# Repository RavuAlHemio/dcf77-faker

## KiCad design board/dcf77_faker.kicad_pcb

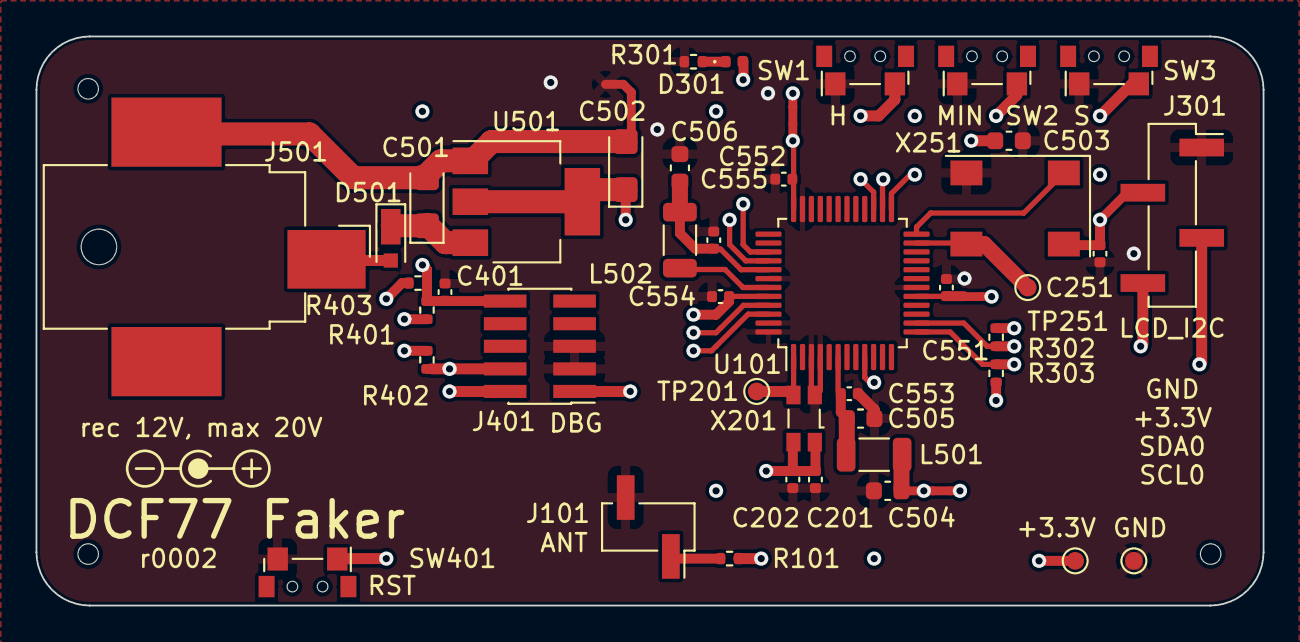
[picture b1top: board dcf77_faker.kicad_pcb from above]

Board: 4 copper layers, 69.0 x 32.0 mm, 46 parts (0 on the bottom side), 27 nets.

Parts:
C201, C202, C251, C401, C551, C552, C553, C554, C555: 100nF; C_0402_1005Metric
C501, C502: 10µF; CP_EIA-3216-18_Kemet-A
C503, C504, C505: 10µF; C_0603_1608Metric
C506: 1µF; C_0603_1608Metric
D301: LED; LED_0402_1005Metric
D501: MSS1P3L-M3/89A; D_MicroSMP_AK
J101: ANT; PinHeader_1x02_P2.54mm_Vertical_SMD_Pin1Right
J301: LCD_I2C; PinHeader_1x04_P2.54mm_Vertical_SMD_Pin1Right
J401: DBG; PinHeader_2x05_P1.27mm_Vertical_SMD
J501: Barrel_Jack; BarrelJack_CUI_PJ-036AH-SMT_Horizontal
L501, L502: 10µH; L_1206_3216Metric
NT501, NT502, NT503, NT504: NetTie_2; NetTie-2_SMD_Pad0.5mm
R101, R402: 1kΩ; R_0402_1005Metric
R301, R401: 330Ω; R_0402_1005Metric
R302, R303: 1.5kΩ; R_0402_1005Metric
R403: 2.2kΩ; R_0402_1005Metric
SW1: H; Shou_Han_TS24CA
SW2: MIN; Shou_Han_TS24CA
SW3: S; Shou_Han_TS24CA
SW401: RST; Shou_Han_TS24CA
TP201, TP251, TP501, TP502: TestPoint; TestPoint_Pad_D1.0mm
U101: ATSAML21G18B-AUT; TQFP-48_7x7mm_P0.5mm
U501: NCP1117ST33T3G; SOT-223-3_TabPin2
X201: 32.768kHz; Oscillator_SMD_SeikoEpson_SG3030CM
X251: 31MHz; Oscillator_SMD_Microchip_DSC8001A-6Pin_7.0x5.0mm_HandSolder

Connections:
/+3.3V: C201.2, C202.2, C251.2, C502.1, J301.2, J401.1, NT502.2, NT504.2, R302.1, R303.1, R402.2, R403.2, TP501.1, U501.2 (VO), X201.1 (VIO), X201.4 (Vcc), X251.4 (Vcc)
/GND: C201.1, C202.1, C251.1, C401.1, C503.2, C504.2, C505.2, C506.2, C551.2, C552.2, C553.2, C554.2, C555.2, J101.2, J301.1, J401.3, J401.5, NT501.2, R301.1, SW1.1, SW2.1, SW3.1, SW401.2, TP502.1, U101.3 (PA02), U101.4 (PA03), U101.18 (GND), U101.35 (GND), U101.42 (GND), U101.47 (PB02), U101.48 (PB03), X201.2 (GND), X251.2 (GND)
/H: SW1.2, U101.27 (PA18)
/LED: D301.2 (A), U101.39 (PA27)
/MIN: SW2.2, U101.26 (PA17)
/S: SW3.2, U101.25 (PA16)
/SCL0: J301.4, R302.2, U101.14 (PA09)
/SDA0: J301.3, R303.2, U101.13 (PA08)
/TCC0WO0: R101.2, U101.9 (PA04)
/VDDANA: C505.1, C553.1, L501.2, U101.6 (VDDANA)
/VDDCORE: C506.1, C555.1, L502.1, U101.41 (VDDCORE)
/VDDIN: C504.1, C554.1, L501.1, NT504.1, U101.44 (VDDIN)
/VDDIO1: C551.1, NT503.2, U101.17 (VDDIO1)
/VDDIO2: C503.1, C552.1, NT502.1, NT503.1, U101.36 (VDDIO2)
/VSW: L502.2, U101.43 (VSW)
/XIN: TP251.1, U101.23 (PA14), X251.3 (OUT)
/XIN32: TP201.1, U101.1 (PA00), X201.3 (OUT)
/X~ST: U101.24 (PA15), X251.1 (~ST)
/debug & reset/SWCLK: J401.4, R402.1, U101.45 (PA30)
/debug & reset/SWDIO: J401.2, U101.46 (PA31)
/debug & reset/~RST: C401.2, J401.10, R401.1, R403.1, U101.40 (~RESET)
/power supply/RAWGND: C501.2, C502.2, J501.2, NT501.1, U501.1 (GND)
unnamed: D301.1 (K), R301.2
unnamed: D501.2 (A), J501.1
unnamed: C501.1, D501.1 (K), U501.3 (VI)
unnamed: J101.1, R101.1
unnamed: R401.2, SW401.1

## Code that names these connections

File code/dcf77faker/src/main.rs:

#![no_std]
#![no_main]


mod calibration;
mod i2c_controller;
mod init;
mod pin;
mod pwm;
mod rtc;
mod sync_vcell;


use core::panic::PanicInfo;

use atsaml21g18b::{interrupt, Peripherals};
use cortex_m_rt::entry;

use crate::pin::PeripheralIndex;


#[inline]
fn noppage() {
    for _ in 0..65536 {
        cortex_m::asm::nop();
    }
}


#[panic_handler]
fn panicked(_reason: &PanicInfo) -> ! {
    let peripherals = unsafe {
        // ain't no rest for the wicked
        Peripherals::steal()
    };

    // set up for blinky LED
    board_pin!(set_io, peripherals, PA, 27);
    board_pin!(make_output, peripherals, PA, 27);

    loop {
        board_pin!(set_high, peripherals, PA, 27);
        noppage();
        board_pin!(set_low, peripherals, PA, 27);
        noppage();
    }
}


#[entry]
fn main() -> ! {
    let mut peripherals = Peripherals::take()
        .expect("peripherals already taken?!");

    crate::init::initialize_microcontroller(&mut peripherals);

    // set pins as I/O:
    // PA16 = input with pull-up (reset-seconds button)
    // PA17 = input with pull-up (increment-minute button)
    // PA18 = input with pull-up (increment-hour button)
    // PA27 = output (LED)
    board_pin!(set_io, peripherals, PA, 16, 17, 18, 27);
    board_pin!(make_input, peripherals, PA, 16, 17, 18);
    board_pin!(enable_pull, peripherals, PA, 16, 17, 18);
    board_pin!(set_high, peripherals, PA, 16, 17, 18);
    board_pin!(make_output, peripherals, PA, 27);

    // hand over pins to peripherals:
    // PA04 = TCC0/WO[0] (E)
    // PA08 = SERCOM0/PAD[0] (C)
    // PA09 = SERCOM0/PAD[1] (C)
    board_pin!(set_peripheral, peripherals, PA, 4, 8, 9);
    board_pin!(select_peripheral, peripherals, PeripheralIndex::E, PA, 4);
    board_pin!(select_peripheral, peripherals, PeripheralIndex::C, PA, 8, 9);

    loop {
    }
}


#[interrupt]
fn RTC() {
    // TODO
}

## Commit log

2022-12-17 initial commit of current board status
2022-12-17 board: align schematic to grid
2022-12-17 board: add buttons to set hour/minute or reset second
2022-12-18 code: µC initialization
2022-12-19 board: reorder HMS button pins
    this increases planarity of the PCB tracks
2022-12-19 board: remove PRL file
    it only contains project data relevant to the local machine
2022-12-19 board: force VDDIO1 and VDDIO2 to be independent nets
    otherwise the name of the common net will keep changing
2022-12-19 board: cleanup of odds and ends
    more spacing in the schematic, better pours on the PCB
2022-12-19 code: initial pin setup
2022-12-20 code: initial work on I2C controller logic
2022-12-20 code: rework I2C error structures
2022-12-20 code: add I2C receive code
2022-12-20 code: i2c: also enable clocks
2022-12-20 code: add PWM code using TCC
2022-12-21 code: add RTC support
2022-12-21 code: pwm: fix comment links
2022-12-21 code: add sync_vcell
    a VolatileCell that pretends to be Sync
2022-12-21 code: add I2C LCD code
2022-12-21 code: add SysTick-based clock
2022-12-21 code: bring it all together
2022-12-21 code: add DCF77 encoding
2023-01-09 board: fix button LCSC number
    we still had the flat ones
2023-01-09 board: slight PCB tweaks, more info
2023-01-10 board: replace X2 with 7x5mm footprint (Microchip DSC8001A)
    this should make it easier to hand-solder after programming
2023-01-10 board: exclude net ties (do not actually exist) and X2 (DNP) from BOM
2023-04-02 update some files to KiCad 7
2023-04-02 hand-solder X2, fix newly-detected DRC violations
2023-04-06 board: allow disabling X2
2023-04-06 board: move RST to make space for battery input
2023-04-06 board: extend lines in power supply box to create rectangle
2023-04-06 board: hierarchical sheets, renumber components
